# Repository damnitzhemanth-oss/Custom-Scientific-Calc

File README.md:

# Navigation 

This repo mainly contains four sections, 
1. CAD for OnShape step files.
2. Images for PCB and CAD images.
3. PCB for project files and production files (POS,CSV,BOM,Gerbers).
4. Firmware for code.

**production folders contain two CSV's, one is manual made with cost and other is KiCad Generated**

# Scientific Calculator 

Scientific calculators are just normal calculator and all other weird math symbols from trigonometry , algebra etc.

These are usually costly and bulky. So I reverse engineered and built one !.

# Architecture of the REPO

```

Custom-Scientific-Calc
├── CAD
│   ├── Assembly.step
│   ├── Base_Plate.step
│   └── Top_Plate.step
├── Images
│   ├── CAD
│   │   ├── Base_P_B.png
│   │   ├── Base_PlateH.png
│   │   ├── Hero_View_Final.png
│   │   ├── Top_Plate.png
│   │   └── Top_Plate_H.png
│   └── PCB
│       ├── Base
│       │   ├── PCB
│       │   │   ├── 3D.png
│       │   │   ├── 3D_B.png
│       │   │   ├── 3D_Hero.png
│       │   │   ├── B.cu.png
│       │   │   ├── F.cu.png
│       │   │   └── HeroView_PCB.png
│       │   └── Schematic
│       │       ├── Battery.png
│       │       ├── Boosters.png
│       │       ├── Connectors.png
│       │       ├── Crystal.png
│       │       ├── LEDs.png
│       │       ├── MCU_Core.png
│       │       ├── Programming.png
│       │       └── Reset_BTN.png
│       └── Top
│           ├── PCB
│           │   ├── 3DB.png
│           │   ├── 3DF.png
│           │   ├── 3DH.png
│           │   ├── PCBB.cu.png
│           │   ├── PCBF.cu.png
│           │   └── PCBH.png
│           └── Schematic
│               ├── Connectors.png
│               ├── LCD.png
│               ├── Power.png
│               └── Switch_Matrix.png
├── PCB
│   ├── Base_PCB
│   │   ├── CAD
│   │   │   ├── BASE_PCB.cad
│   │   │   └── BASE_PCB.step
│   │   └── Project_Files
│   │       ├── BASE.kicad_sch
│   │       ├── BASE_PCB.kicad_pcb
│   │       ├── BASE_PCB.kicad_pro
│   │       ├── BASE_PCB.step
│   │       └── Production
│   │           ├── BASE.csv
│   │           ├── BASE_PCB-all-pos.csv
│   │           └── BasePCB_Gerbers.zip
│   └── Top_PCB
│       ├── CAD
│       │   ├── TOP.step
│       │   └── Top_PCB.cad
│       └── Project_Files
│           ├── Production
│           │   ├── TOP-all-pos.csv
│           │   ├── TOP.csv
│           │   └── TopPCB_Gerbers.zip
│           ├── TOP.kicad_pcb
│           ├── TOP.kicad_pro
│           ├── TOP.kicad_sch
│           └── TOP.step
├── README.md
└── firmware
    ├── include
    │   ├── board.h
    │   ├── keypad.h
    │   └── lcd.h
    ├── single_file
    │   └── main.c
    └── src
        ├── keyboard.c
        ├── lcd.c
        └── main.c

```

# BOM 

## BASE PCB BOM

| # | Ref | Part / Value | Qty | Footprint | LCSC | Unit $ | Total $ |
|---|-----|--------------|-----|-----------|------|--------|---------|
| 1 | U1 | STM32L431RCT6 | 1 | LQFP-64 10x10mm | C92468 | $3.60 | $3.60 |
| 2 | U02 | XCL108B331ER-G (3.3V boost) | 1 | CL-2025-02 | — | $2.50 | $2.50 |
| 3 | U03 | XCL108B501ER-G (5.0V boost) | 1 | CL-2025-02 | — | $2.50 | $2.50 |
| 4 | U4 | EVQ-P0P02B (reset button) | 1 | SW-SMD_EVQ-P0P02B | C6554563 | $0.44 | $0.44 |
| 5 | BT1 | Keystone 103 CR2032 holder | 1 | BatteryHolder_Keystone_103 | — | $0.55 | $0.55 |
| 6 | Y1 | 32.768 kHz crystal, 12.5pF | 1 | Crystal_SMD_3225-4Pin | C32346 | $0.28 | $0.28 |
| 7 | C1–C5, C14, C16, C18 | 100nF 50V X7R | 8 | C_0402_1005 | C1525 | $0.01 | $0.08 |
| 8 | C6 | 1µF 10V X5R | 1 | C_0402_1005 | C15849 | $0.02 | $0.02 |
| 9 | C7, C15 | 10µF 10V X5R | 2 | C_0402_1005 | C19702 | $0.03 | $0.06 |
| 10 | C10, C11, C12, C17, C21 | 10µF 10V X5R | 5 | C_0805_2012 | C15850 | $0.05 | $0.25 |
| 11 | C19, C20 | 18pF 50V C0G | 2 | C_0402_1005 | C1579 | $0.01 | $0.02 |
| 12 | R1, R2 | 1kΩ 1% | 2 | R_0402_1005 | C11702 | $0.005 | $0.01 |
| 13 | R3, R8 | 10kΩ 1% | 2 | R_0402_1005 | C25744 | $0.005 | $0.01 |
| 14 | R7 | 10Ω 1% | 1 | R_0402_1005 | C103090 | $0.005 | $0.005 |
| 15 | D1 | Green LED 0603 | 1 | LED_0603_1608 | C72043 | $0.03 | $0.03 |
| 16 | D2 | Red LED 0603 | 1 | LED_0603_1608 | C2286 | $0.03 | $0.03 |
| 17 | J1, J2 | 1×13 pin header, 2.00mm | 2 | PinHeader_1x13_P2.00 | — | $0.30 | $0.60 |
| 18 | J4 | 2×3 pin header, 2.54mm (SWD) | 1 | PinHeader_2x03_P2.54 | C65104 | $0.08 | $0.08 |

**BASE Subtotal: ~$11.07**

---

## TOP PCB BOM

| # | Ref | Part / Value | Qty | Footprint | LCSC | Unit $ | Total $ |
|---|-----|--------------|-----|-----------|------|--------|---------|
| 1 | U1–U48 | EVQ-P0P02B tactile switches | 48 | SW-SMD_EVQ-P0P02B_3d | C6554563 | $0.44 | $21.12 |
| 2 | D1–D48 | 1N4148W (anti-ghosting) | 48 | D_SOD-110 | C89641 | $0.01 | $0.48 |
| 3 | SW1 | PS-5824SVA-6PLW (latching power switch) | 1 | SW-SMD_6P-L5.8-W5.8-P2.00 | C47018553 | $1.00 | $1.00 |
| 4 | J1, J2 | 1×13 socket, 2.00mm | 2 | PinSocket_1x13_P2.00 | — | $0.35 | $0.70 |
| 5 | J3 | Hirose FH12-10S-0.5SH (LCD FPC) | 1 | FFC-FPC_Hirose_FH12-10S | C506791 | $0.60 | $0.60 |
| 6 | DS1 | Sharp LS027B7DH01A 2.7" Memory LCD | 1 | *external, soldered via J3* | — | $18.00 | $18.00 |

**TOP Subtotal: ~$41.90**

---

## COMBINED SUMMARY

| Item | Cost |
|------|------|
| BASE PCB components | $11.07 |
| TOP PCB components | $41.90 |
| **Total component cost** | **$52.97** |
| PCB fabrication (2 boards, 5 pcs each, JLCPCB) | ~$15.00 |
| SMT assembly setup fee | ~$8.00 |
| Extended part feeder fees (~15 parts × $1.50) | ~$22.50 |
| Stencil + labor | ~$6.50 |
| **Estimated total (5 units)** | **~$105 per run** |
| **Per unit (5 units)** | **~$21 + shipping** |

---

## Notes

Torex boosters footprint was not available on internet so I created symbol and footprint.

# CAD 

Onshape Link : https://cad.onshape.com/documents/ad7319a20d75441a919925a9/w/2019cd65cfda231ca2b84125/e/7e9bc9015b0e0043ba3c4c11

How assembly works: Base PCB and top PCB latches onto each other and gets sandwiched between Top_Plate and Base_Plate preferably with 16mm screws.

# Schematic 

I used two torex boosters to boost 3v from Coin Cell into 5V for LCD and 3.3V for other components.

And matrix connection was used for 48 switches.

# Firmware

This is a test firmware. Not yet tested yet. Available as single file or 6 files (easier for debugging).

# AI USAGE

AI was used for help of Firmware and debugging problems with OnShape.

# Gallery 

**View more images in *images* folder**

## Gallery

### PCB — Base

### PCB — Top

### Schematic — Base

### Schematic — Top

### CAD

# License

MIT License, freedom to use any of the files in the repo. But credit is appreciated!

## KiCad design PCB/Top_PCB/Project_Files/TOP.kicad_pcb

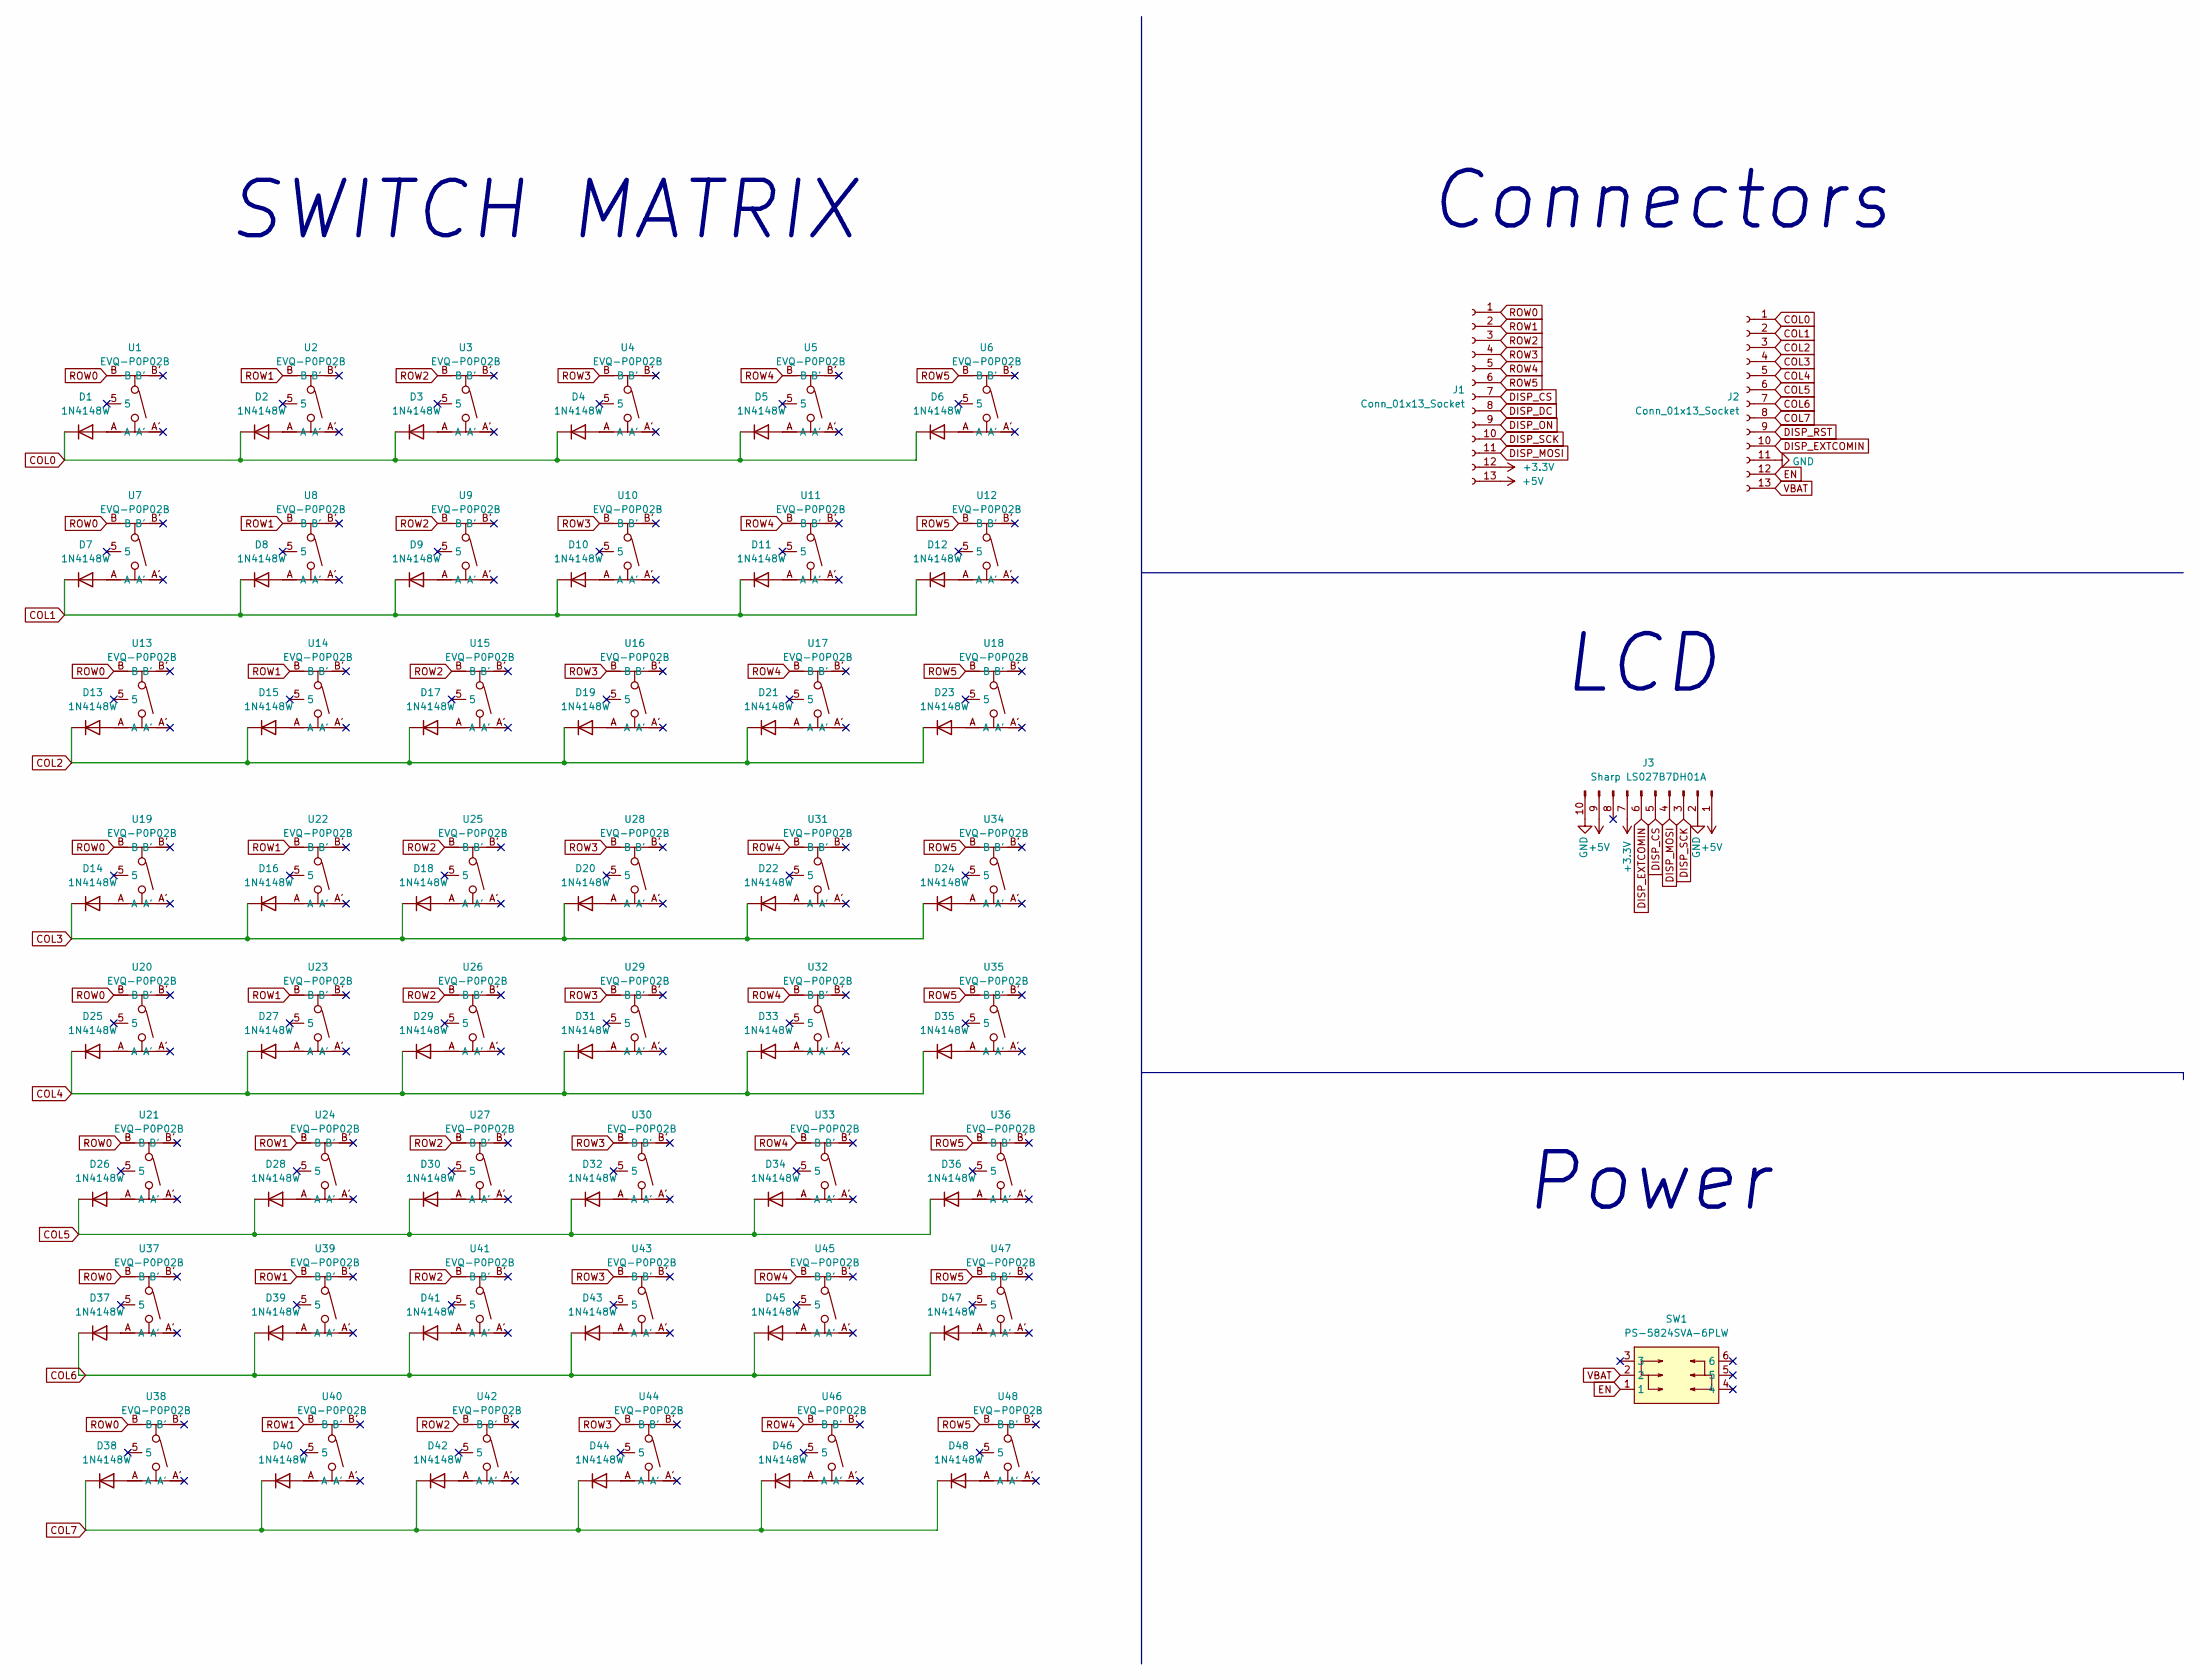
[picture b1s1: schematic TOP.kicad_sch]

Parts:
D1, D2, D3, D4, D5, D6, D7, D8, D9, D10, D11, D12, D13, D14, D15, D16, D17, D18, D19, D20, D21, D22, D23, D24, D25, D26, D27, D28, D29, D30, D31, D32, D33, D34, D35, D36, D37, D38, D39, D40, D41, D42, D43, D44, D45, D46, D47, D48: 1N4148W; D_SOD-110
J1, J2: Conn_01x13_Socket; PinSocket_1x13_P2.00mm_Vertical
J3: Sharp LS027B7DH01A; Hirose_FH12-10S-0.5SH_1x10-1MP_P0.50mm_Horizontal
SW1: PS-5824SVA-6PLW; SW-SMD_6P-L5.8-W5.8-P2.00-LS11.3; MPN PS-5824SVA-6PLW; LCSC Part C47018553
U1, U2, U3, U4, U5, U6, U7, U8, U9, U10, U11, U12, U13, U14, U15, U16, U17, U18, U19, U20, U21, U22, U23, U24, U25, U26, U27, U28, U29, U30, U31, U32, U33, U34, U35, U36, U37, U38, U39, U40, U41, U42, U43, U44, U45, U46, U47, U48: EVQ-P0P02B; SW-SMD_EVQ-P0P02B_3d; MPN EVQ-P0P02B; LCSC Part C6554563

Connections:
+3.3V: J1.12, J3.7
+5V: J1.13, J3.1, J3.9
COL0: D1.1 (K), D2.1 (K), D3.1 (K), D4.1 (K), D5.1 (K), D6.1 (K), J2.1
COL1: D7.1 (K), D8.1 (K), D9.1 (K), D10.1 (K), D11.1 (K), D12.1 (K), J2.2
COL2: D13.1 (K), D15.1 (K), D17.1 (K), D19.1 (K), D21.1 (K), D23.1 (K), J2.3
COL3: D14.1 (K), D16.1 (K), D18.1 (K), D20.1 (K), D22.1 (K), D24.1 (K), J2.4
COL4: D25.1 (K), D27.1 (K), D29.1 (K), D31.1 (K), D33.1 (K), D35.1 (K), J2.5
COL5: D26.1 (K), D28.1 (K), D30.1 (K), D32.1 (K), D34.1 (K), D36.1 (K), J2.6
COL6: D37.1 (K), D39.1 (K), D41.1 (K), D43.1 (K), D45.1 (K), D47.1 (K), J2.7
COL7: D38.1 (K), D40.1 (K), D42.1 (K), D44.1 (K), D46.1 (K), D48.1 (K), J2.8
DISP_CS: J1.7, J3.5
DISP_DC: J1.8
DISP_EXTCOMIN: J2.10, J3.6
DISP_MOSI: J1.11, J3.4
DISP_ON: J1.9
DISP_RST: J2.9
DISP_SCK: J1.10, J3.3
EN: J2.12, SW1.1
GND: J2.11, J3.2, J3.10
unnamed: D1.2 (A), U1.A
unnamed: D2.2 (A), U2.A
unnamed: D3.2 (A), U3.A
unnamed: D4.2 (A), U4.A
unnamed: D5.2 (A), U5.A
unnamed: D6.2 (A), U6.A
unnamed: D7.2 (A), U7.A
unnamed: D8.2 (A), U8.A
unnamed: D9.2 (A), U9.A
unnamed: D10.2 (A), U10.A
unnamed: D11.2 (A), U11.A
unnamed: D12.2 (A), U12.A
unnamed: D13.2 (A), U13.A
unnamed: D14.2 (A), U19.A
unnamed: D15.2 (A), U14.A
unnamed: D16.2 (A), U22.A
unnamed: D17.2 (A), U15.A
unnamed: D18.2 (A), U25.A
unnamed: D19.2 (A), U16.A
unnamed: D20.2 (A), U28.A
unnamed: D21.2 (A), U17.A
unnamed: D22.2 (A), U31.A
unnamed: D23.2 (A), U18.A
unnamed: D24.2 (A), U34.A
unnamed: D25.2 (A), U20.A
unnamed: D26.2 (A), U21.A
unnamed: D27.2 (A), U23.A
unnamed: D28.2 (A), U24.A
unnamed: D29.2 (A), U26.A
unnamed: D30.2 (A), U27.A
unnamed: D31.2 (A), U29.A
unnamed: D32.2 (A), U30.A
unnamed: D33.2 (A), U32.A
unnamed: D34.2 (A), U33.A
unnamed: D35.2 (A), U35.A
unnamed: D36.2 (A), U36.A
unnamed: D37.2 (A), U37.A
unnamed: D38.2 (A), U38.A
unnamed: D39.2 (A), U39.A
unnamed: D40.2 (A), U40.A
unnamed: D41.2 (A), U41.A
unnamed: D42.2 (A), U42.A
unnamed: D43.2 (A), U43.A
unnamed: D44.2 (A), U44.A
unnamed: D45.2 (A), U45.A
unnamed: D46.2 (A), U46.A
unnamed: D47.2 (A), U47.A
unnamed: D48.2 (A), U48.A
ROW0: J1.1, U1.B, U7.B, U13.B, U19.B, U20.B, U21.B, U37.B, U38.B
ROW1: J1.2, U2.B, U8.B, U14.B, U22.B, U23.B, U24.B, U39.B, U40.B
ROW2: J1.3, U3.B, U9.B, U15.B, U25.B, U26.B, U27.B, U41.B, U42.B
ROW3: J1.4, U4.B, U10.B, U16.B, U28.B, U29.B, U30.B, U43.B, U44.B
ROW4: J1.5, U5.B, U11.B, U17.B, U31.B, U32.B, U33.B, U45.B, U46.B
ROW5: J1.6, U6.B, U12.B, U18.B, U34.B, U35.B, U36.B, U47.B, U48.B
VBAT: J2.13, SW1.2

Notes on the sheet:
Power
LCD
Connectors
SWITCH MATRIX

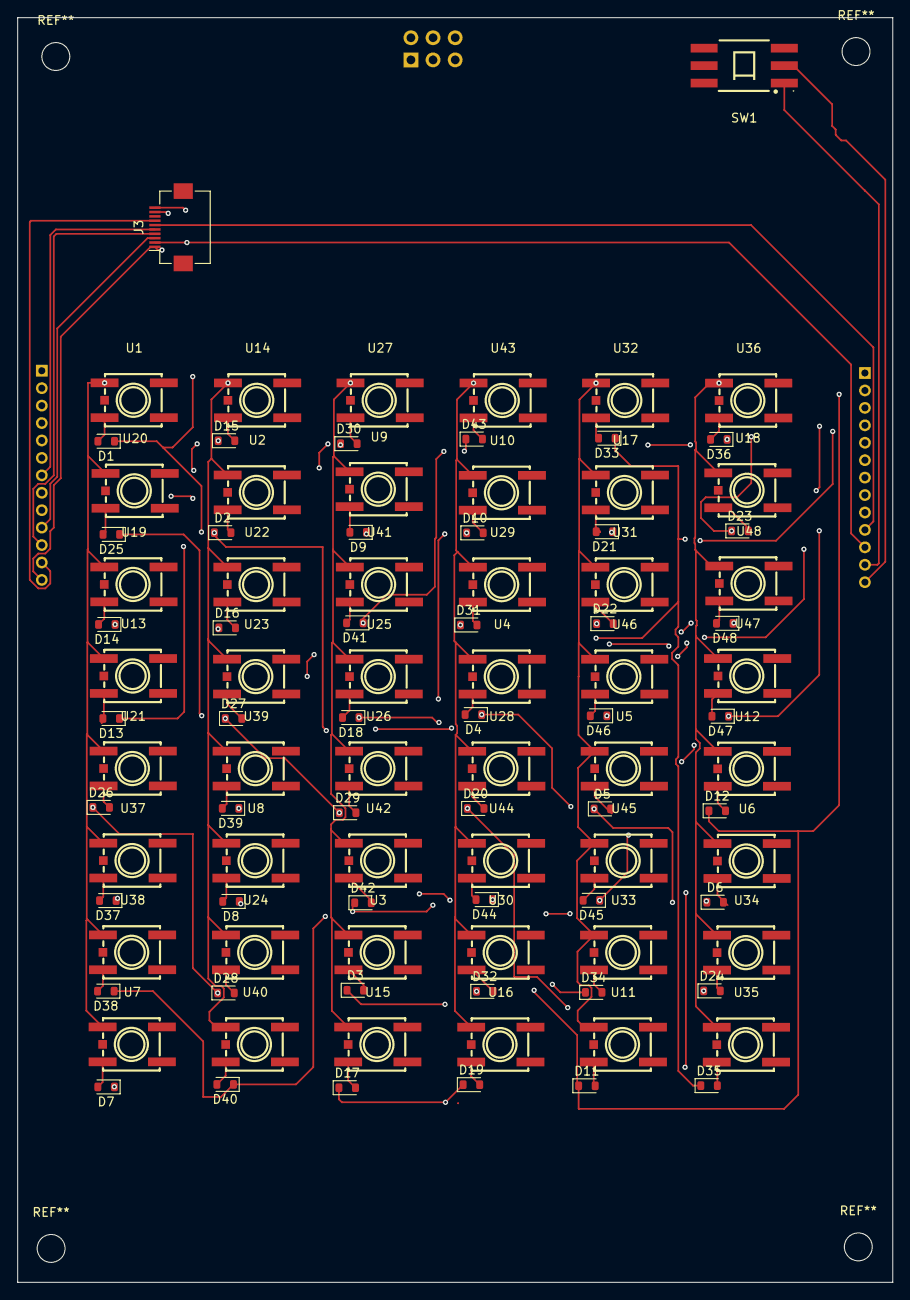
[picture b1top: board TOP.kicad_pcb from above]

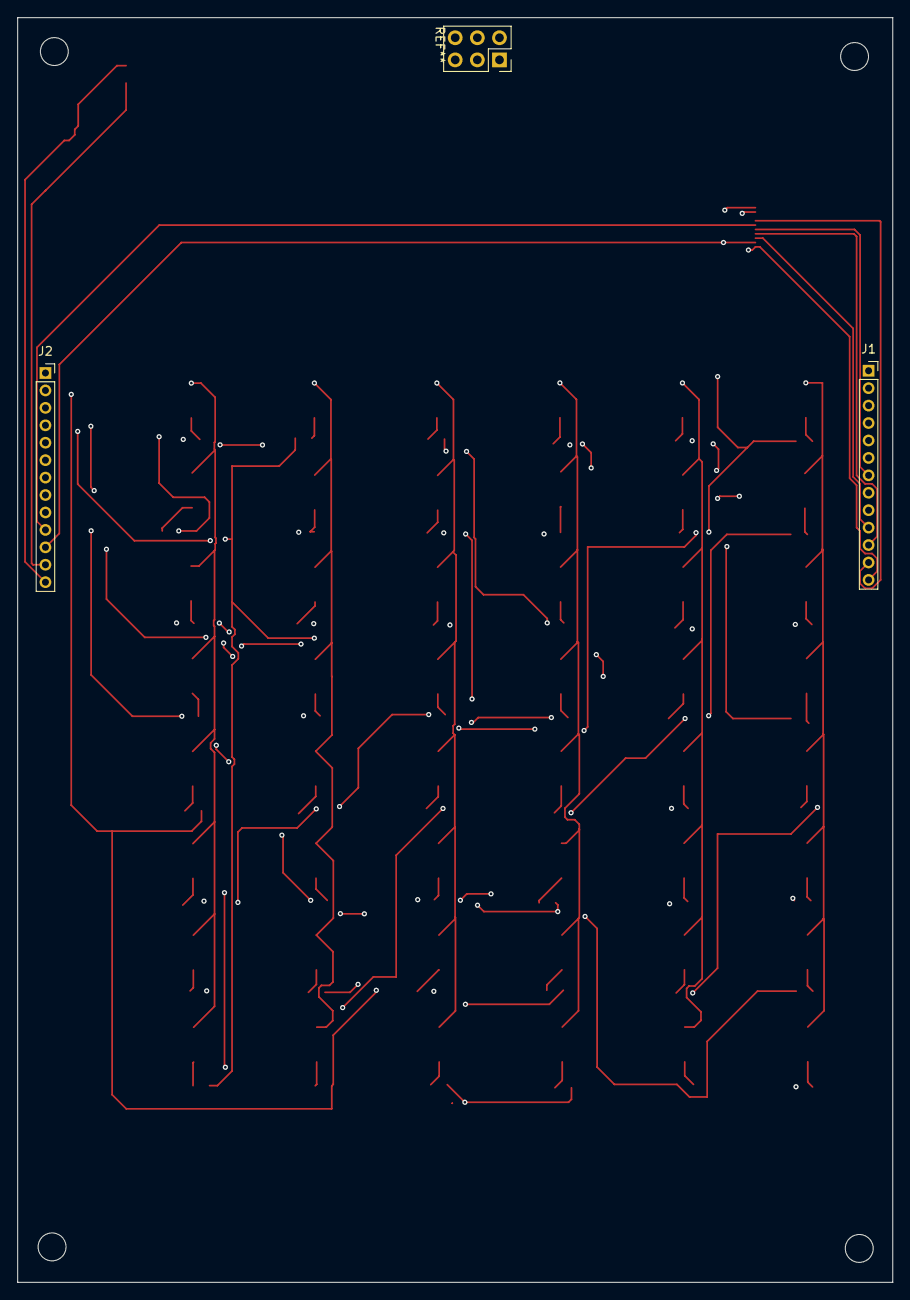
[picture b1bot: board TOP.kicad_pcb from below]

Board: 2 copper layers, 100.4 x 145.1 mm, 100 parts (2 on the bottom side), 71 nets.

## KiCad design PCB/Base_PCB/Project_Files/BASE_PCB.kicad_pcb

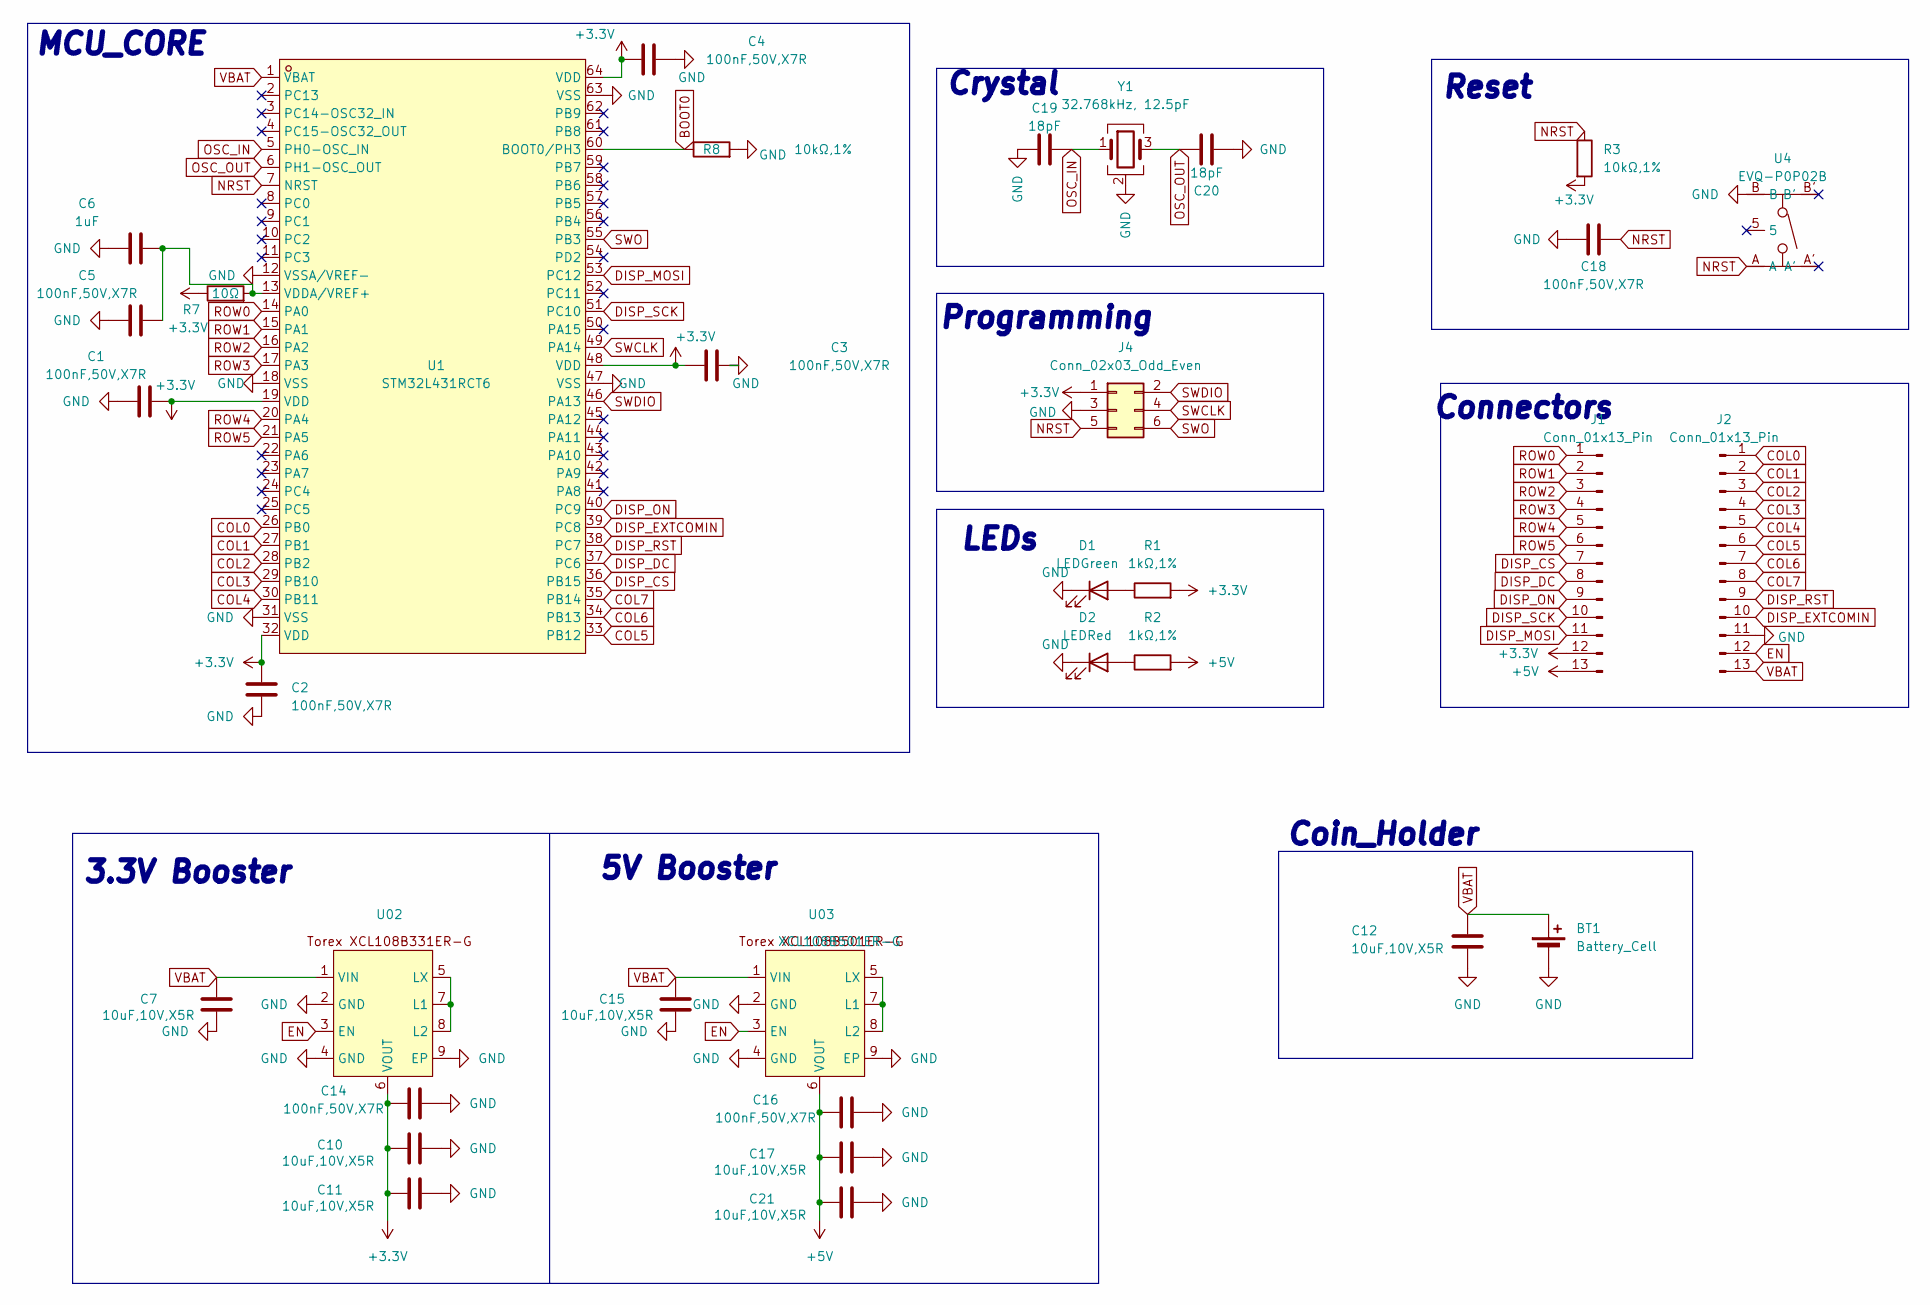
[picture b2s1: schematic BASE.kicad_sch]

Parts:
BT1: Battery_Cell; BatteryHolder_Keystone_103_1x20mm
C1, C2, C3, C4, C5, C14, C16, C18: 100nF,50V,X7R; C_0402_1005Metric
C6: 1uF; C_0402_1005Metric
C7, C15: 10uF,10V,X5R; C_0402_1005Metric
C10, C11, C12, C17, C21: 10uF,10V,X5R; C_0805_2012Metric
C19, C20: 18pF; C_0402_1005Metric
D1: LEDGreen; LED_0603_1608Metric
D2: LEDRed; LED_0603_1608Metric
J1, J2: Conn_01x13_Pin; PinHeader_1x13_P2.00mm_Vertical
J4: Conn_02x03_Odd_Even; PinHeader_2x03_P2.54mm_Vertical
R1, R2: 1kΩ,1%; R_0402_1005Metric
R3, R8: 10kΩ,1%; R_0402_1005Metric
R7: 10Ω; R_0402_1005Metric
U1: STM32L431RCT6; LQFP-64_L10.0-W10.0-P0.50-LS12.0-BL; MPN STM32L431RCT6; LCSC Part C92468
U02: CL-2025-02
U03: XCL108B501ER-G; CL-2025-02
U4: EVQ-P0P02B; SW-SMD_EVQ-P0P02B; MPN EVQ-P0P02B; LCSC Part C6554563
Y1: 32.768kHz, 12.5pF; Crystal_SMD_3225-4Pin_3.2x2.5mm

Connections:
+3.3V: C1.2, C2.1, C3.1, C4.1, C10.1, C11.1, C14.1, J1.12, J4.1, R1.2, R3.2, R7.1, U1.19 (VDD), U1.32 (VDD), U1.48 (VDD), U1.64 (VDD), U02.6 (VOUT)
+5V: C16.1, C17.1, C21.1, J1.13, R2.2, U03.6 (VOUT)
BOOT0: R8.1, U1.60 (BOOT0/PH3)
COL0: J2.1, U1.26 (PB0)
COL1: J2.2, U1.27 (PB1)
COL2: J2.3, U1.28 (PB2)
COL3: J2.4, U1.29 (PB10)
COL4: J2.5, U1.30 (PB11)
COL5: J2.6, U1.33 (PB12)
COL6: J2.7, U1.34 (PB13)
COL7: J2.8, U1.35 (PB14)
DISP_CS: J1.7, U1.36 (PB15)
DISP_DC: J1.8, U1.37 (PC6)
DISP_EXTCOMIN: J2.10, U1.39 (PC8)
DISP_MOSI: J1.11, U1.53 (PC12)
DISP_ON: J1.9, U1.40 (PC9)
DISP_RST: J2.9, U1.38 (PC7)
DISP_SCK: J1.10, U1.51 (PC10)
EN: J2.12, U02.3 (EN), U03.3 (EN)
GND: BT1.2 (-), C1.1, C2.2, C3.2, C4.2, C5.1, C6.1, C7.2, C10.2, C11.2, C12.2, C14.2, C15.2, C16.2, C17.2, C18.1, C19.1, C20.1, C21.2, D1.1 (K), D2.1 (K), J2.11, J4.3, R8.2, U1.12 (VSSA/VREF-), U1.18 (VSS), U1.31 (VSS), U1.47 (VSS), U1.63 (VSS), U02.2 (GND), U02.4 (GND), U02.9 (EP), U03.2 (GND), U03.4 (GND), U03.9 (EP), U4.B, Y1.2 (G), Y1.4 (G)
NRST: C18.2, J4.5, R3.1, U1.7 (NRST), U4.A
unnamed: D1.2 (A), R1.1
unnamed: D2.2 (A), R2.1
unnamed: C5.2, C6.2, R7.2, U1.13 (VDDA/VREF+)
unnamed: U02.5 (LX), U02.7 (L1), U02.8 (L2)
unnamed: U03.5 (LX), U03.7 (L1), U03.8 (L2)
OSC_IN: C19.2, U1.5 (PH0-OSC_IN), Y1.1
OSC_OUT: C20.2, U1.6 (PH1-OSC_OUT), Y1.3
ROW0: J1.1, U1.14 (PA0)
ROW1: J1.2, U1.15 (PA1)
ROW2: J1.3, U1.16 (PA2)
ROW3: J1.4, U1.17 (PA3)
ROW4: J1.5, U1.20 (PA4)
ROW5: J1.6, U1.21 (PA5)
SWCLK: J4.4, U1.49 (PA14)
SWDIO: J4.2, U1.46 (PA13)
SWO: J4.6, U1.55 (PB3)
VBAT: BT1.1 (+), C7.1, C12.1, C15.1, J2.13, U1.1 (VBAT), U02.1 (VIN), U03.1 (VIN)

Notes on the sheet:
LEDs
Reset
3.3V Booster
MCU_CORE
Programming
Coin_Holder
Connectors
5V Booster
Crystal

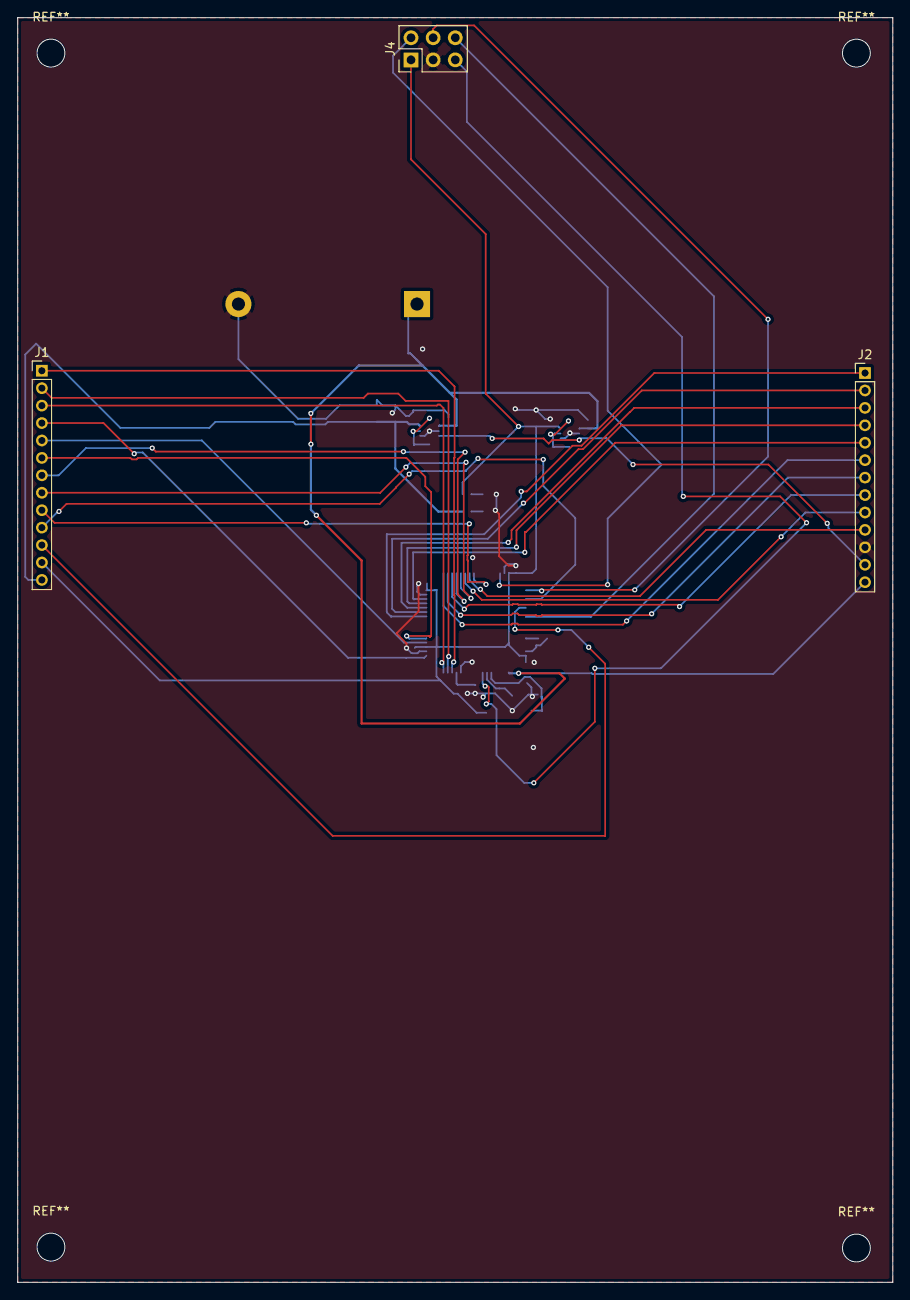
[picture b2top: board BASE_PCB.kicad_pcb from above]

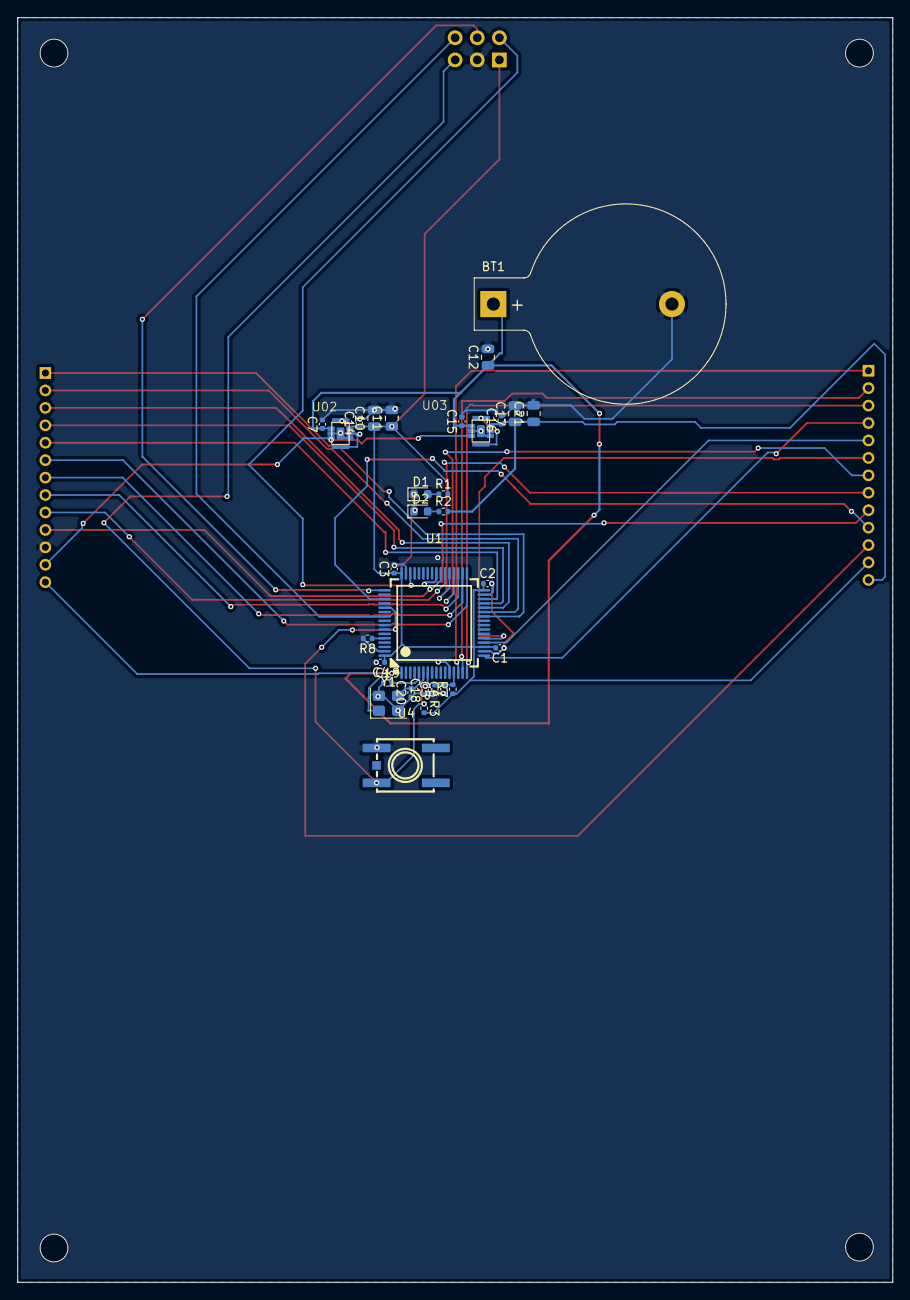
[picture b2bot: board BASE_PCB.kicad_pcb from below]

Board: 2 copper layers, 100.4 x 145.1 mm, 34 parts (31 on the bottom side), 38 nets.

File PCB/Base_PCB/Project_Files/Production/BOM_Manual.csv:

| # | Ref | Part / Value | Qty | Footprint | LCSC | Unit $ | Total $ |
|---|-----|--------------|-----|-----------|------|--------|---------|
| 1 | U1 | STM32L431RCT6 | 1 | LQFP-64 10x10mm | C92468 | $3.60 | $3.60 |
| 2 | U02 | XCL108B331ER-G (3.3V boost) | 1 | CL-2025-02 | — | $2.50 | $2.50 |
| 3 | U03 | XCL108B501ER-G (5.0V boost) | 1 | CL-2025-02 | — | $2.50 | $2.50 |
| 4 | U4 | EVQ-P0P02B (reset button) | 1 | SW-SMD_EVQ-P0P02B | C6554563 | $0.44 | $0.44 |
| 5 | BT1 | Keystone 103 CR2032 holder | 1 | BatteryHolder_Keystone_103 | — | $0.55 | $0.55 |
| 6 | Y1 | 32.768 kHz crystal, 12.5pF | 1 | Crystal_SMD_3225-4Pin | C32346 | $0.28 | $0.28 |
| 7 | C1–C5, C14, C16, C18 | 100nF 50V X7R | 8 | C_0402_1005 | C1525 | $0.01 | $0.08 |
| 8 | C6 | 1µF 10V X5R | 1 | C_0402_1005 | C15849 | $0.02 | $0.02 |
| 9 | C7, C15 | 10µF 10V X5R | 2 | C_0402_1005 | C19702 | $0.03 | $0.06 |
| 10 | C10, C11, C12, C17, C21 | 10µF 10V X5R | 5 | C_0805_2012 | C15850 | $0.05 | $0.25 |
| 11 | C19, C20 | 18pF 50V C0G | 2 | C_0402_1005 | C1579 | $0.01 | $0.02 |
| 12 | R1, R2 | 1kΩ 1% | 2 | R_0402_1005 | C11702 | $0.005 | $0.01 |
| 13 | R3, R8 | 10kΩ 1% | 2 | R_0402_1005 | C25744 | $0.005 | $0.01 |
| 14 | R7 | 10Ω 1% | 1 | R_0402_1005 | C103090 | $0.005 | $0.005 |
| 15 | D1 | Green LED 0603 | 1 | LED_0603_1608 | C72043 | $0.03 | $0.03 |
| 16 | D2 | Red LED 0603 | 1 | LED_0603_1608 | C2286 | $0.03 | $0.03 |
| 17 | J1, J2 | 1×13 pin header, 2.00mm | 2 | PinHeader_1x13_P2.00 | — | $0.30 | $0.60 |
| 18 | J4 | 2×3 pin header, 2.54mm (SWD) | 1 | PinHeader_2x03_P2.54 | C65104 | $0.08 | $0.08 |

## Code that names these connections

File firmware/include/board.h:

#ifndef BOARD_H
#define BOARD_H

#include "stm32l4xx_hal.h"

#define ROW0_PORT   GPIOA
#define ROW0_PIN    GPIO_PIN_0
#define ROW1_PORT   GPIOA
#define ROW1_PIN    GPIO_PIN_1
#define ROW2_PORT   GPIOA
#define ROW2_PIN    GPIO_PIN_2
#define ROW3_PORT   GPIOA
#define ROW3_PIN    GPIO_PIN_3
#define ROW4_PORT   GPIOA
#define ROW4_PIN    GPIO_PIN_4
#define ROW5_PORT   GPIOA
#define ROW5_PIN    GPIO_PIN_5

#define COL0_PORT   GPIOB
#define COL0_PIN    GPIO_PIN_0
#define COL1_PORT   GPIOB
#define COL1_PIN    GPIO_PIN_1
#define COL2_PORT   GPIOB
#define COL2_PIN    GPIO_PIN_2
#define COL3_PORT   GPIOB
#define COL3_PIN    GPIO_PIN_10
#define COL4_PORT   GPIOB
#define COL4_PIN    GPIO_PIN_11
#define COL5_PORT   GPIOB
#define COL5_PIN    GPIO_PIN_12
#define COL6_PORT   GPIOB
#define COL6_PIN    GPIO_PIN_13
#define COL7_PORT   GPIOB
#define COL7_PIN    GPIO_PIN_14

#define NUM_ROWS    6
#define NUM_COLS    8

#define LCD_SCK_PORT    GPIOC
#define LCD_SCK_PIN     GPIO_PIN_10
#define LCD_MOSI_PORT   GPIOC
#define LCD_MOSI_PIN    GPIO_PIN_12
#define LCD_CS_PORT     GPIOB
#define LCD_CS_PIN      GPIO_PIN_15
#define LCD_DC_PORT     GPIOC
#define LCD_DC_PIN      GPIO_PIN_6
#define LCD_RST_PORT    GPIOC
#define LCD_RST_PIN     GPIO_PIN_7
#define LCD_ON_PORT     GPIOC
#define LCD_ON_PIN      GPIO_PIN_9
#define LCD_EXTCOMIN_PORT  GPIOC
#define LCD_EXTCOMIN_PIN   GPIO_PIN_8

#define LCD_WIDTH       400
#define LCD_HEIGHT      240
#define LCD_LINE_BYTES  ((LCD_WIDTH / 8) + 2)

extern SPI_HandleTypeDef hspi3;

#endif
